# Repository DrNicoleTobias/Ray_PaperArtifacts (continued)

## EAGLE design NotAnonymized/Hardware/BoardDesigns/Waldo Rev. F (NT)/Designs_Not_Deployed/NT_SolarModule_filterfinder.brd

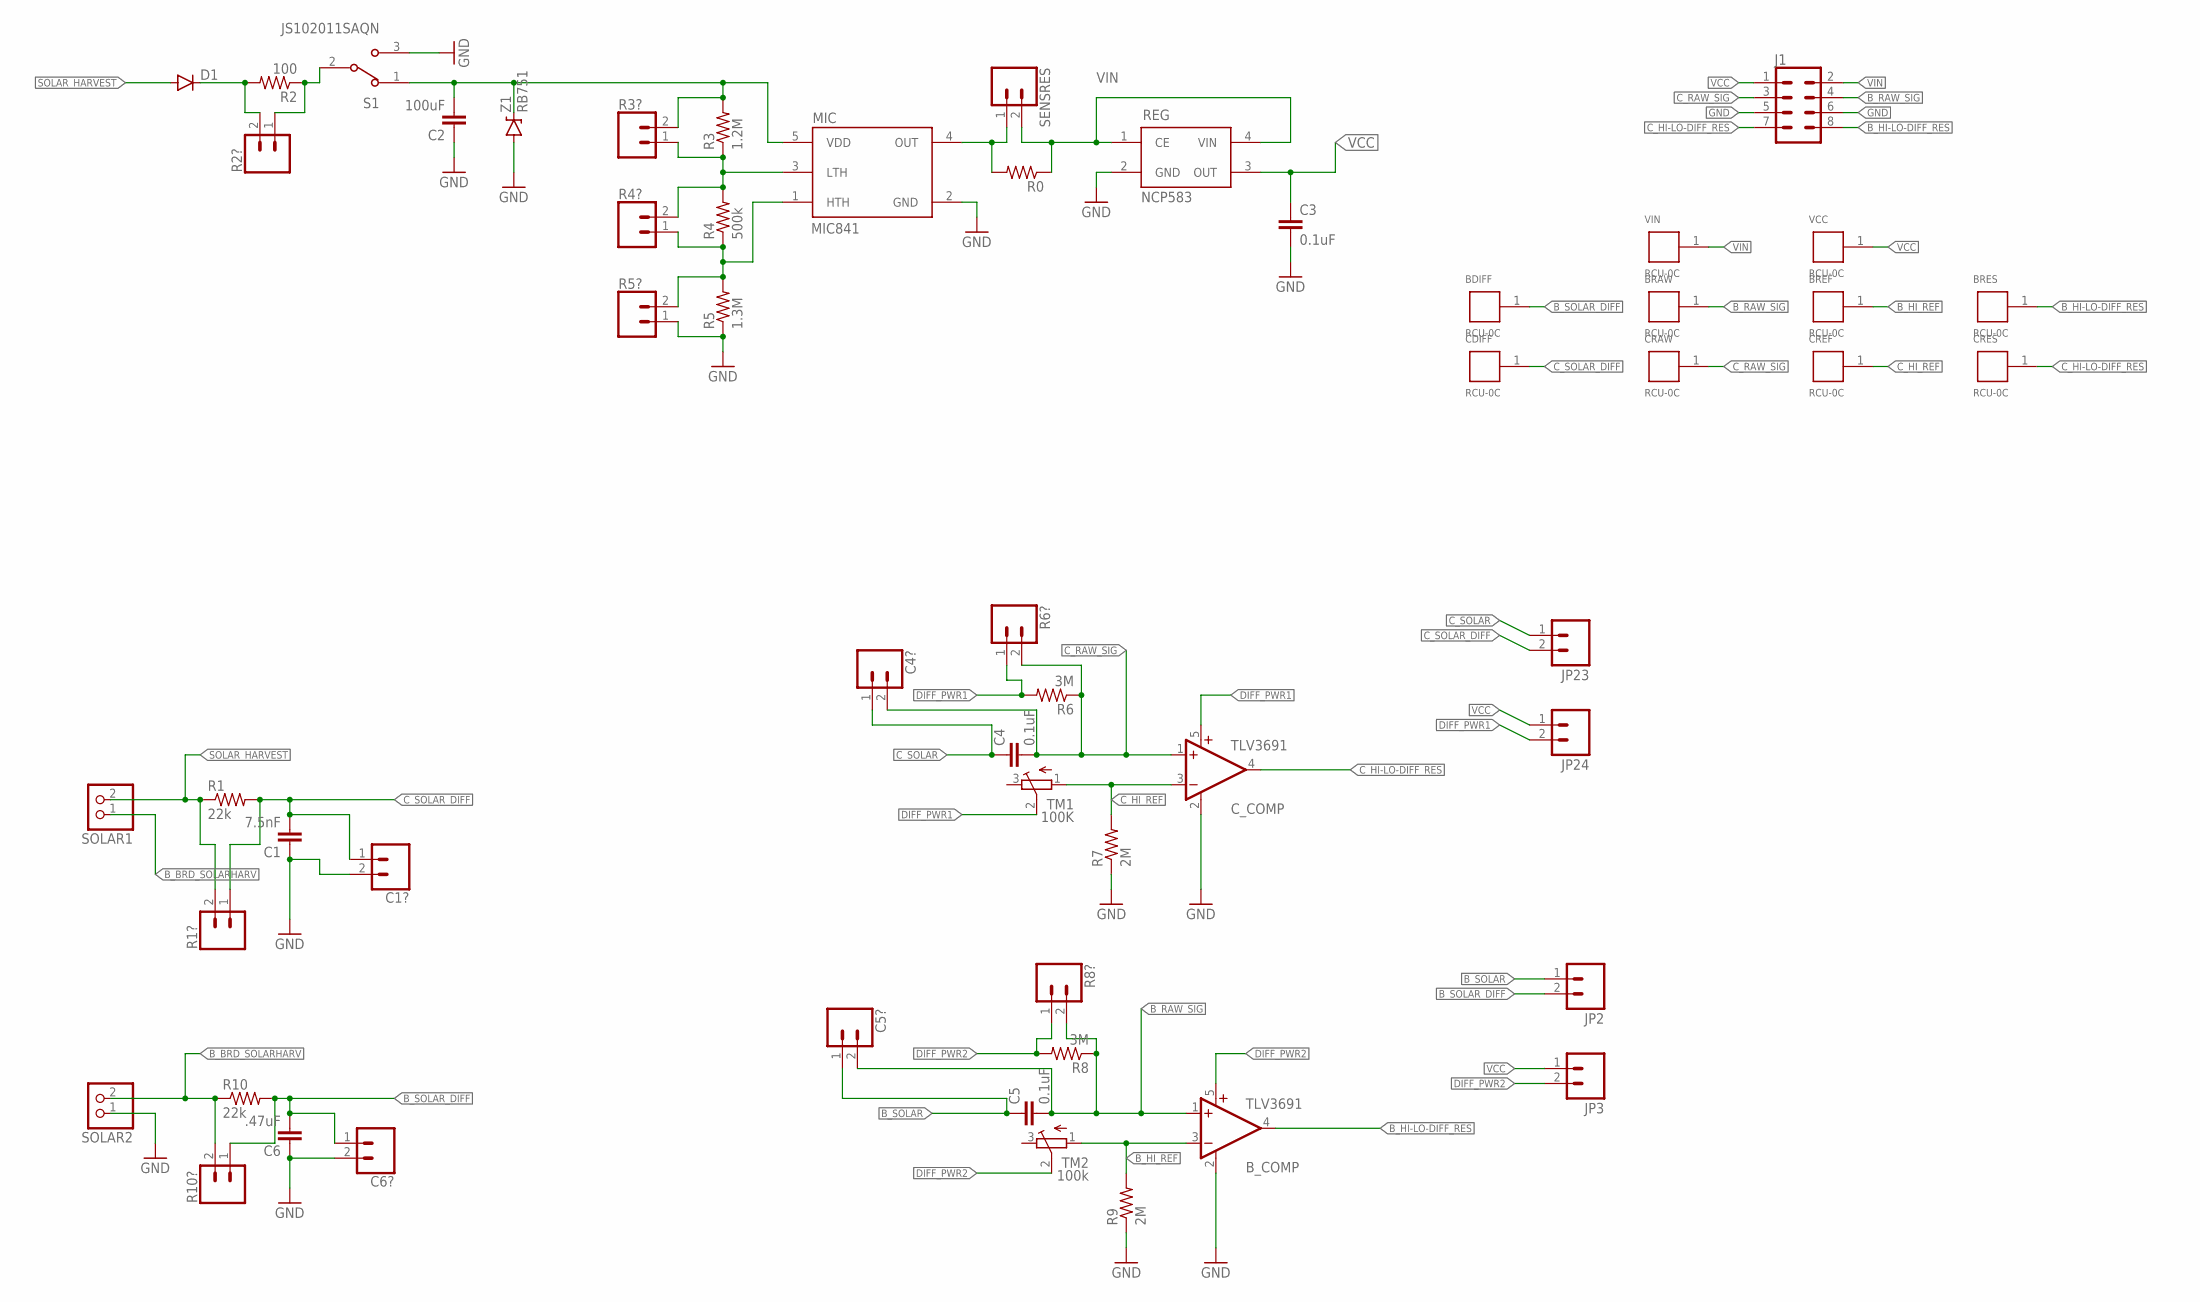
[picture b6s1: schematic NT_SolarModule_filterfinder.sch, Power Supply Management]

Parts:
BDIFF: RCU-0C; TE_RCU-0C
BRAW: RCU-0C; TE_RCU-0C
BREF: RCU-0C; TE_RCU-0C
BRES: RCU-0C; TE_RCU-0C
B_COMP: TLV3691; SC70-5
C1: 7.5nF; 0603-CAP
C1?, C4?, C5?, C6?: CONN_02; 1X02
C2: 100uF; 0603-CAP
C3, C4, C5: 0.1uF; 0603-CAP
C6: .47uF; 0603-CAP
CDIFF: RCU-0C; TE_RCU-0C
CRAW: RCU-0C; TE_RCU-0C
CREF: RCU-0C; TE_RCU-0C
CRES: RCU-0C; TE_RCU-0C
C_COMP: TLV3691; SC70-5
D1: DIODESOD523; SOD523
J1: CONN_04X2; 2X4
JP2, JP3, JP23, JP24: M02; 1X02-1.27MM
MIC: MIC841; SC70-5
R0: RESISTOR0603; 0603-RES
R1, R10: 22k; 0603-RES
R1?, R2?, R3?, R4?, R5?, R6?, R8?, R10?: CONN_02; 1X02
R2: 100; 0603-RES
R3: 1.2M; 0603-RES
R4: 500k; 0603-RES
R5: 1.3M; 0603-RES
R6, R8: 3M; 0603-RES
R7, R9: 2M; 0603-RES
REG: NCP583; SC82-AB_1PRIMARY
S1: JS102011SAQN; SW_JS102011SAQN
SENSRES: CONN_02; 1X02
SOLAR1, SOLAR2: PINHD-1X2; 1X02
TM1: 100K; TC33X
TM2: 100k; TC33X
VCC: RCU-0C; TE_RCU-0C
VIN: RCU-0C; TE_RCU-0C
Z1: RB751; SOD-523

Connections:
B_BRD_SOLARHARV: R10.1, R10?.2, SOLAR1.1, SOLAR2.2
B_HI-LO-DIFF_RES: BRES.1, B_COMP.4 (OUT), J1.8
B_HI_REF: BREF.1, B_COMP.3 (-IN), R9.2, TM2.1 (A)
B_RAW_SIG: BRAW.1, B_COMP.1 (+IN), C5.2, C5?.2, J1.4, R8.1, R8?.2
B_SOLAR: C5.1, C5?.1, JP2.1
B_SOLAR_DIFF: BDIFF.1, C6.2, C6?.1, JP2.2, R10.2, R10?.1
C_HI-LO-DIFF_RES: CRES.1, C_COMP.4 (OUT), J1.7
C_HI_REF: CREF.1, C_COMP.3 (-IN), R7.2, TM1.1 (A)
C_RAW_SIG: C4.2, C4?.2, CRAW.1, C_COMP.1 (+IN), J1.3, R6.1, R6?.2
C_SOLAR: C4.1, C4?.1, JP23.1
C_SOLAR_DIFF: C1.2, C1?.1, CDIFF.1, JP23.2, R1.2, R1?.1
DIFF_PWR1: C_COMP.5 (V+), JP24.2, R6.2, R6?.1, TM1.2 (S)
DIFF_PWR2: B_COMP.5 (V+), JP3.2, R8.2, R8?.1, TM2.2 (S)
GND: B_COMP.2 (GND), C1.1, C1?.2, C2.1, C3.2, C6.1, C6?.2, C_COMP.2 (GND), J1.5, J1.6, MIC.2 (GND), R5.1, R5?.1, R7.1, R9.1, REG.2 (GND), S1.3, SOLAR2.1, Z1.ANODE (A)
MIC_INPUT: C2.2, MIC.5 (VDD), R3.2, R3?.2, S1.1, Z1.CATHODE (C)
unnamed: D1.C, R2.2, R2?.2
unnamed: MIC.4 (OUT), R0.2, SENSRES.1
unnamed: R2.1, R2?.1, S1.2
unnamed: MIC.3 (LTH), R3.1, R3?.1, R4.2, R4?.2
unnamed: MIC.1 (HTH), R4.1, R4?.1, R5.2, R5?.2
SOLAR_HARVEST: D1.A, R1.1, R1?.2, SOLAR1.2
VCC: C3.1, J1.1, JP3.1, JP24.1, REG.3 (OUT), VCC.1
VIN: J1.2, R0.1, REG.1 (CE), REG.4 (VIN), SENSRES.2, VIN.1

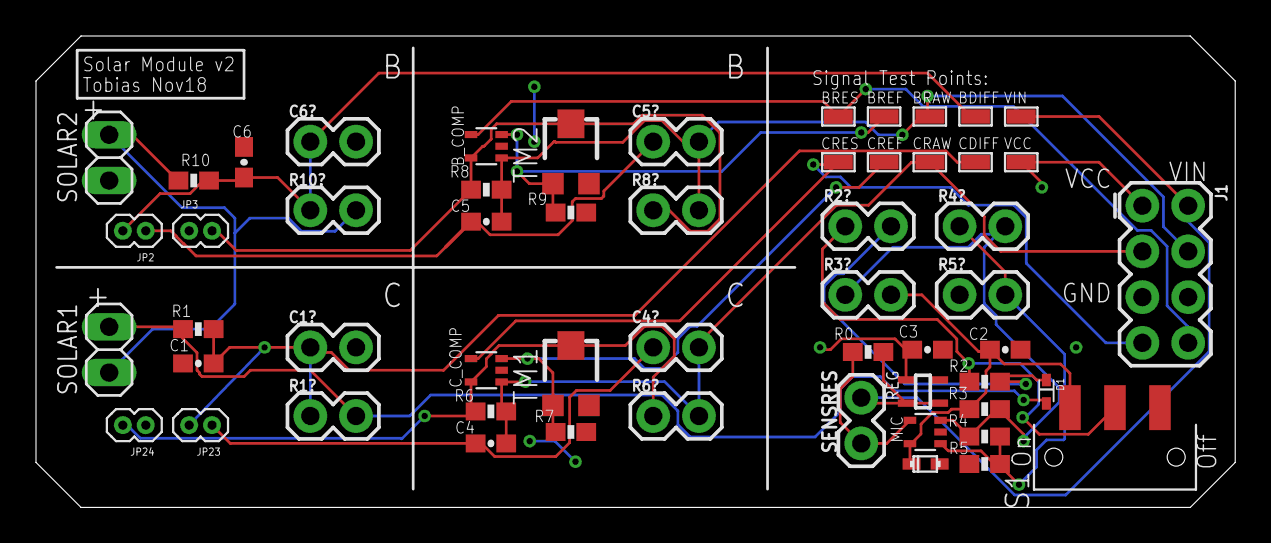
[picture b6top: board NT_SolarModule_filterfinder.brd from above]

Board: 2 copper layers, 66.6 x 26.2 mm, 56 parts (0 on the bottom side), 23 nets.
